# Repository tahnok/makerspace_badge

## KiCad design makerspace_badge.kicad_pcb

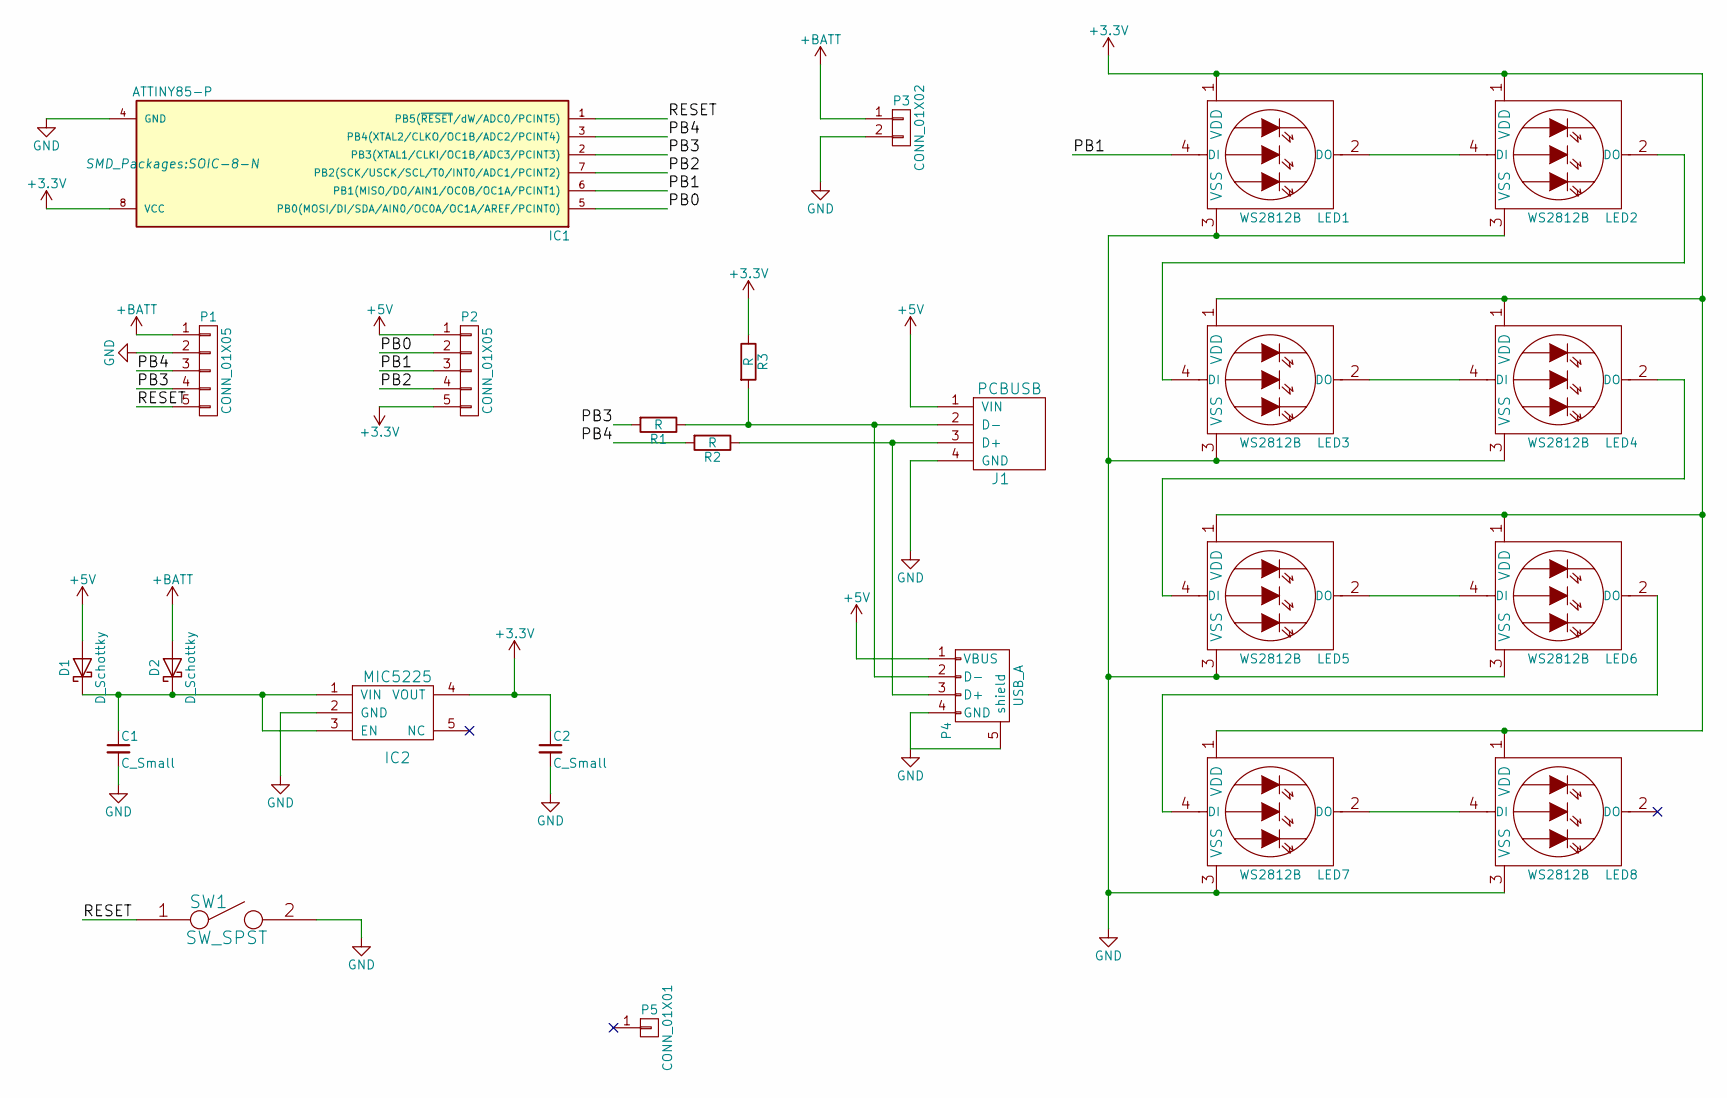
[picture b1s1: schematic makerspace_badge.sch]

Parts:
C1, C2: C_Small; C_0603_HandSoldering
D1, D2: D_Schottky; D_0603
IC1: ATTINY85-P; SOIC-8-N
IC2: MIC5225; SOT-23-5_HandSoldering
J1: PCBUSB
LED1, LED2, LED3, LED4, LED5, LED6, LED7, LED8: WS2812B
P1, P2: CONN_01X05; Socket_Strip_Straight_lock_1x05_Pitch2.54mm
P3: CONN_01X02; JST_PH_S2B-PH-SM4-TB_02x2.00mm_Angled
P4: USB_A; USB_B
P5: CONN_01X01; 1pin
R1, R2, R3: R; R_0603_HandSoldering
SW1: SW_SPST; SW_SPST_B3SL-1002P

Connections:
+3V3: C2.1, IC1.8 (VCC), IC2.4 (VOUT), LED1.1 (VDD), LED2.1 (VDD), LED3.1 (VDD), LED4.1 (VDD), LED5.1 (VDD), LED6.1 (VDD), LED7.1 (VDD), LED8.1 (VDD), P2.5, R3.1
+5V: D1.2 (A), J1.1 (VIN), P2.1, P4.1 (VBUS)
+BATT: D2.2 (A), P1.1, P3.1
/PB0: IC1.5 (PB0(MOSI/DI/SDA/AIN0/OC0A/OC1A/AREF/PCI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), P2.2
/PB1: IC1.6 (PB1(MISO/DO/AIN1/OC0B/OC1A/PCINT1)), LED1.4 (DI), P2.3
/PB2: IC1.7 (PB2(SCK/USCK/SCL/T0/INT0/ADC1/PCINT2)), P2.4
/PB3: IC1.2 (PB3(XTAL1/CLKI/OC1B/ADC3/PCINT3)), P1.4, R1.2
/PB4: IC1.3 (PB4(XTAL2/CLKO/OC1B/ADC2/PCINT4)), P1.3, R2.2
/RESET: IC1.1 (PB5(~RESET~/dW/ADC0/PCINT5)), P1.5, SW1.1
GND: C1.2, C2.2, IC1.4 (GND), IC2.2 (GND), J1.4 (GND), LED1.3 (VSS), LED2.3 (VSS), LED3.3 (VSS), LED4.3 (VSS), LED5.3 (VSS), LED6.3 (VSS), LED7.3 (VSS), LED8.3 (VSS), P1.2, P3.2, P4.4 (GND), P4.5 (shield), SW1.2
unnamed: C1.1, D1.1 (K), D2.1 (K), IC2.1 (VIN), IC2.3 (EN)
unnamed: J1.2 (D-), P4.2 (D-), R1.1, R3.2
unnamed: J1.3 (D+), P4.3 (D+), R2.1
unnamed: LED1.2 (DO), LED2.4 (DI)
unnamed: LED2.2 (DO), LED3.4 (DI)
unnamed: LED3.2 (DO), LED4.4 (DI)
unnamed: LED4.2 (DO), LED5.4 (DI)
unnamed: LED5.2 (DO), LED6.4 (DI)
unnamed: LED6.2 (DO), LED7.4 (DI)
unnamed: LED7.2 (DO), LED8.4 (DI)

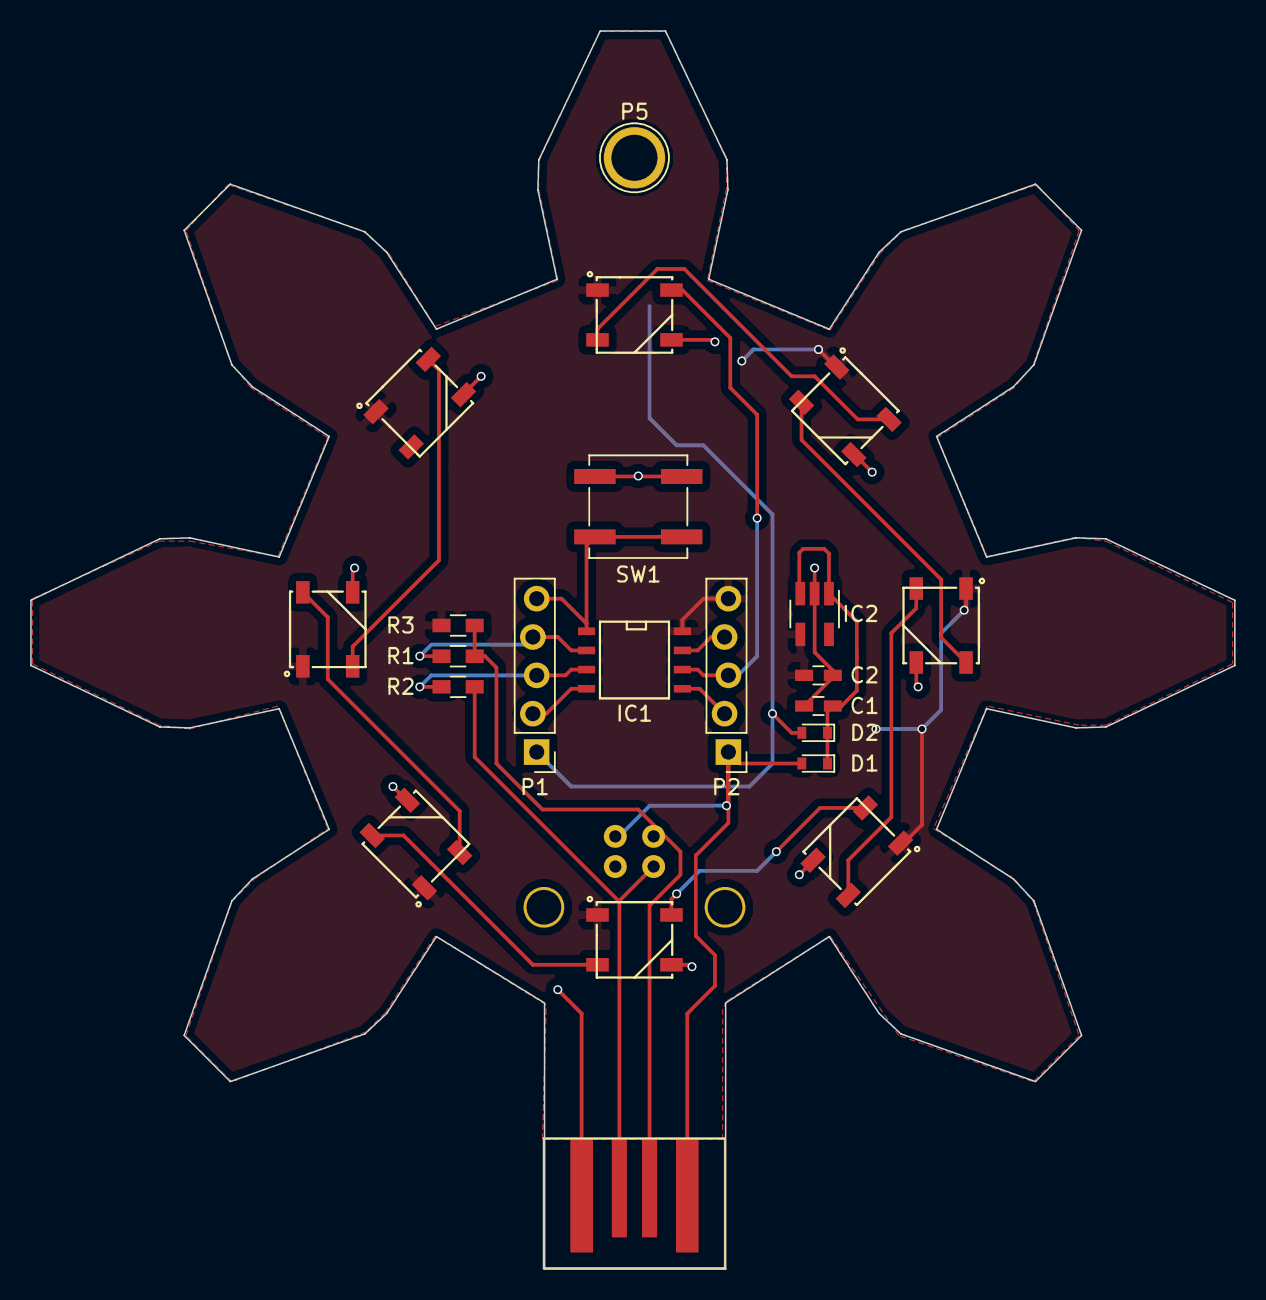
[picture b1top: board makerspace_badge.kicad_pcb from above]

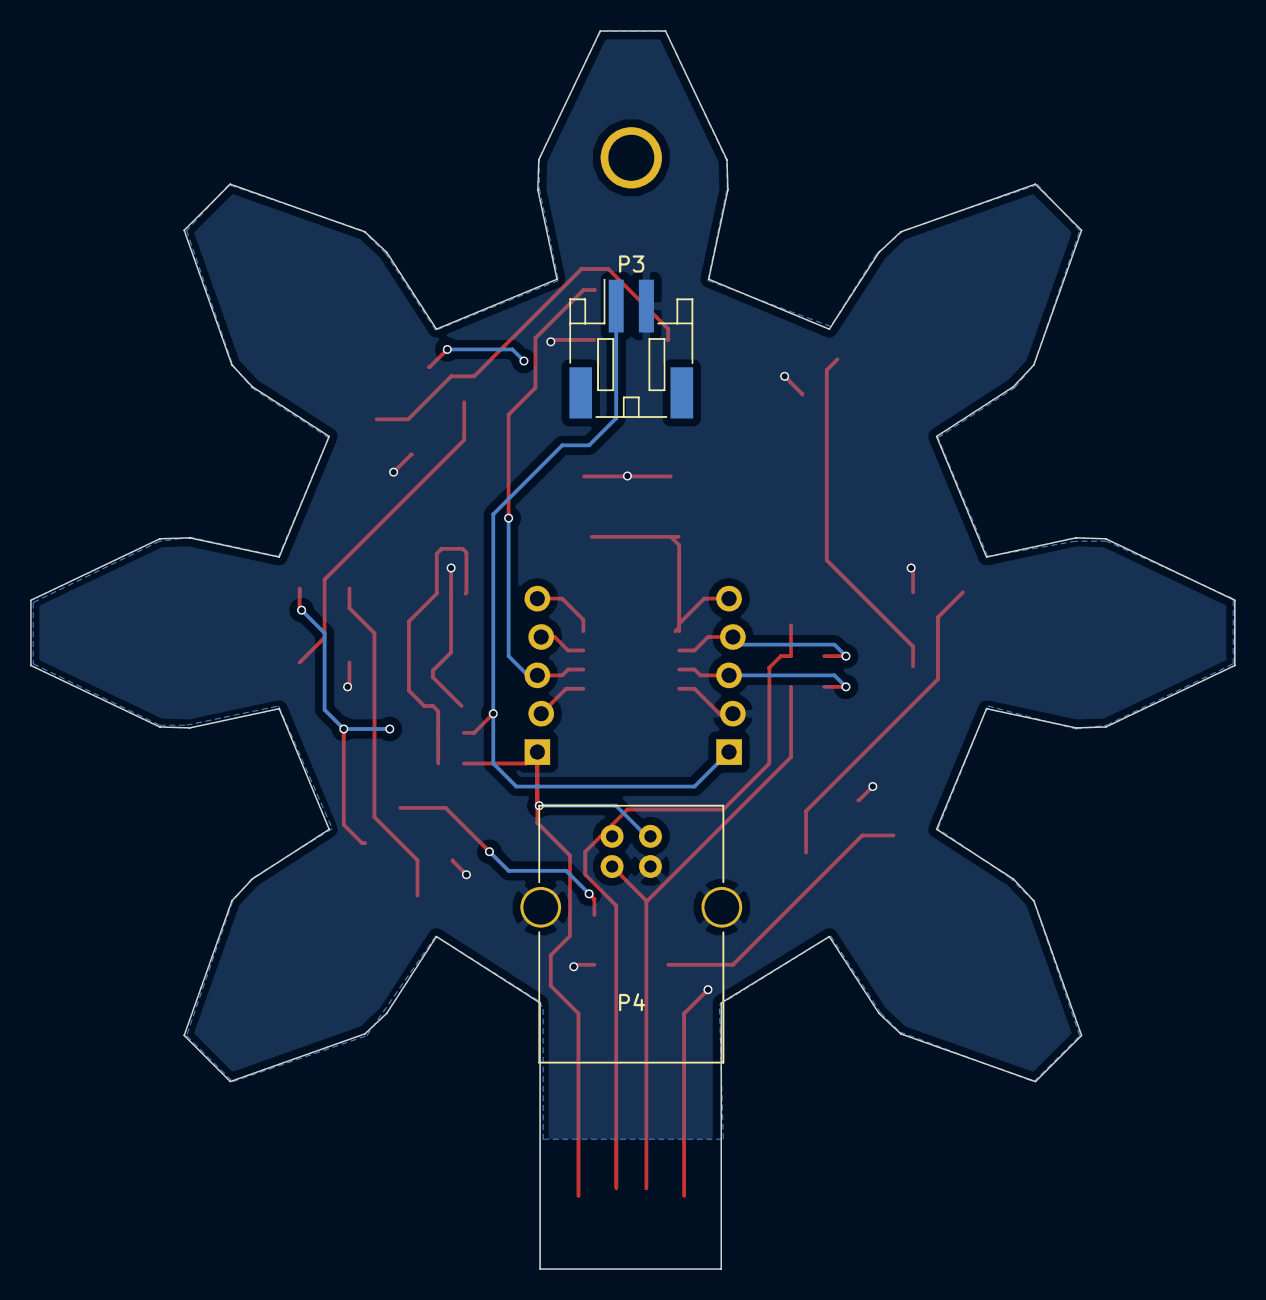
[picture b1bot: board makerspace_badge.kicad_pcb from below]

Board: 2 copper layers, 79.8 x 82.0 mm, 24 parts (2 on the bottom side), 20 nets.

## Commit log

2017-03-20 first version
